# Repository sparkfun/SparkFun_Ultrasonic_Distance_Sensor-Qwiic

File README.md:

SparkFun Ultrasonic Distance Sensor - TCT40 (Qwiic) 
========================================

<center></center>

[*SparkFun Ultrasonic Distance Sensor - TCT40 (Qwiic) (SEN-24805)*](https://www.sparkfun.com/products/24805)

The SparkFun Qwiic Ultrasonic Distance Sensor, a user-friendly upgrade to the popular HC-SR04 sensor, offers non-contact distance measurement from 2cm to 400cm with an accuracy of 3mm. This sensor is designed to seamlessly integrate with the Qwiic ecosystem for I<sup>2</sup>C communication, making it a breeze to add to your existing projects and daisy-chain with other Qwiic components.

If you prefer to bypass the Qwiic connector and I2C, you can also access the VCC, Trigger, Echo, and Ground pins broken out on the board's edge. Please be aware that this ultrasonic sensor comes uncalibrated, and you will need to manipulate the raw output for your specific application.

With its wide range of applications, the SparkFun Qwiic Ultrasonic Distance Sensor is a versatile tool for robotics projects, obstacle avoidance systems, and any application that requires accurate distance measurement without physical contact. Its adaptability makes it a valuable addition to your toolkit.

Repository Contents
-------------------

* **/Documentation** - Datasheets, additional product information
* **/Enclosure** - Enclosure files 
* **/Firmware** - Default firmware on the Ultrasonic Distance Sensor -TCT40 
* **/Hardware** - Eagle design files (.brd, .sch)
* **/Production** - Production panel files (.brd)

Documentation
--------------
* **[Hookup Guide](https://docs.sparkfun.com/SparkFun_Ultrasonic_Distance_Sensor-Qwiic)** - Basic hookup guide for the SparkFun Ultrasonic Distance Sensor - TCT40 (Qwiic).
* **[Arduino Library](https://github.com/sparkfun/SparkFun_Qwiic_Ultrasonic_Arduino_Library)** - Arduino library for the SparkFun Ultrasonic Distance Sensor - TCT40 (Qwiic). 

License Information
-------------------

This product is _**open source**_! 

Please review the LICENSE.md file for license information. 

If you have any questions or concerns on licensing, please contact technical support on our [SparkFun forums](https://forum.sparkfun.com/viewforum.php?f=152).

Distributed as-is; no warranty is given.

- Your friends at SparkFun.

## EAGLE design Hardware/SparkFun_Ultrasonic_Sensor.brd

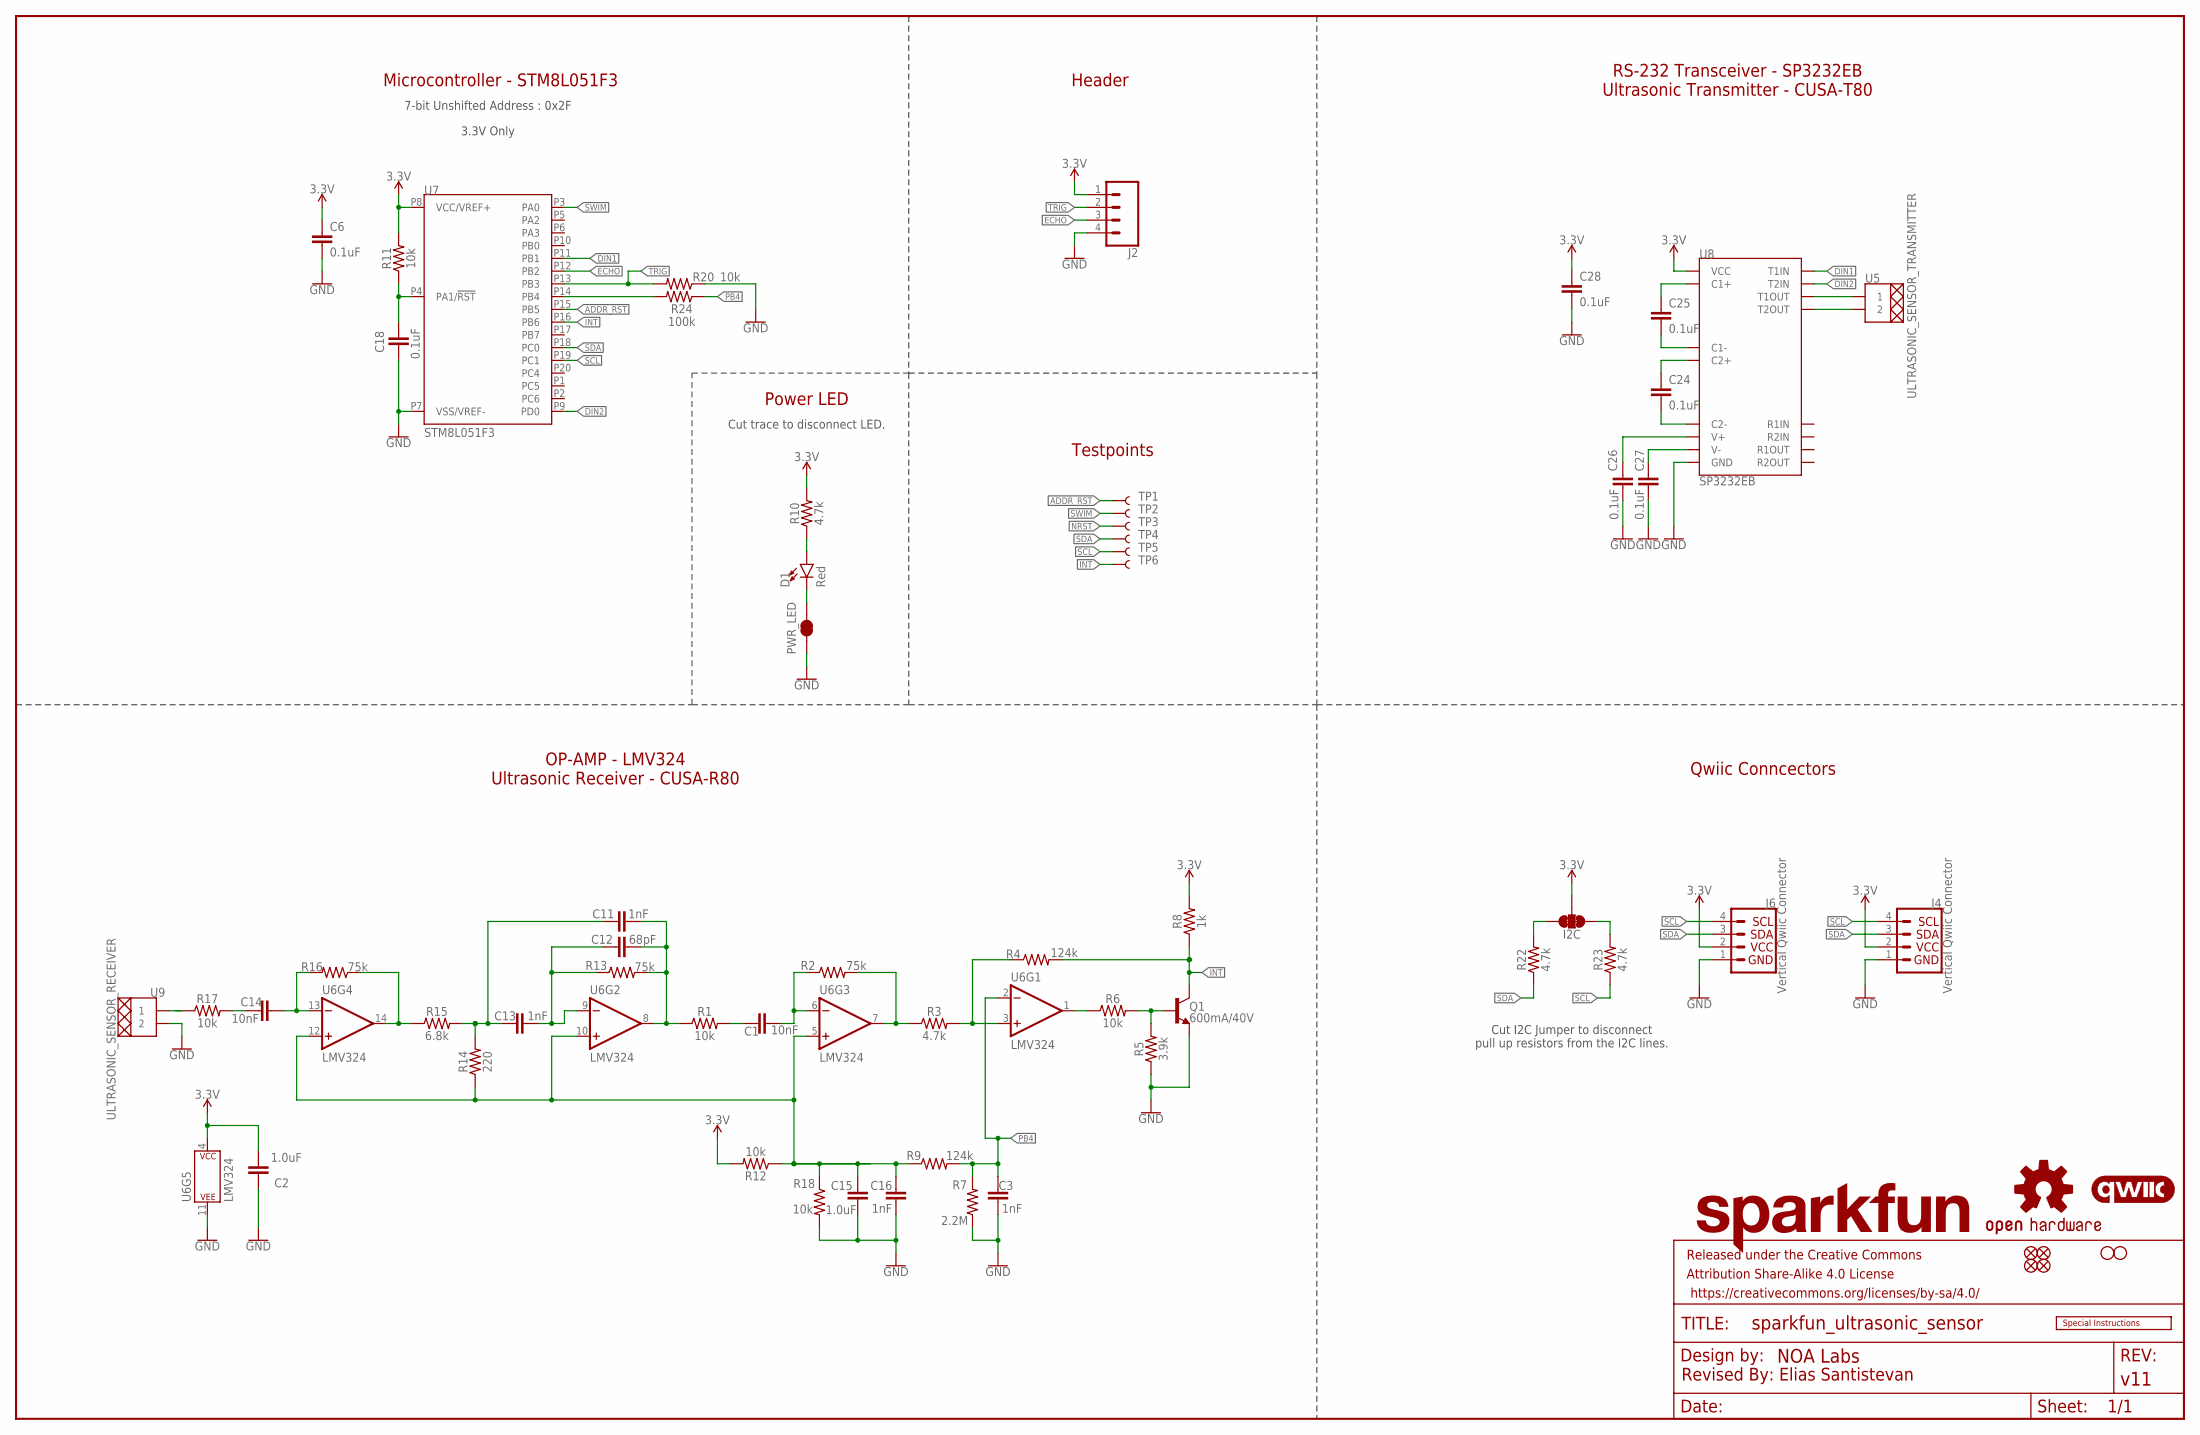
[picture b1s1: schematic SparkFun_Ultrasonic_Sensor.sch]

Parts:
C1, C14: 10nF; 0603
C2, C15: 1.0uF; 0603
C3, C11, C13, C16: 1nF; 0603
C6, C18, C24, C25, C26, C27, C28: 0.1uF; 0603
C12: 68pF; 0603
D1: Red; LED-0603
FD1, FD2, FD3, FD4: FIDUCIAL1X2; FIDUCIAL-1X2
FRAME1: FRAME-LEDGER; CREATIVE_COMMONS
H1, H2: STAND-OFFTIGHT; STAND-OFF-TIGHT
I2C: JUMPER-SMT_3_2-NC_TRACE_SILK; SMT-JUMPER_3_2-NC_TRACE_SILK
J2: CONN_041X04_NO_SILK_NO_POP; 1X04_NO_SILK
J4, J6: Vertical Qwiic Connector; JST04_1MM_VERT
LOGO1: SPECIAL_INSTRUCTIONS-ORDERING; ORDERING_INSTRUCTIONS
LOGO2: SFE_LOGO_NAME.1_INCH; SFE_LOGO_NAME_.1
LOGO3: QWIIC_LOGO_3MM; QWIIC_3MM
LOGO4: OSHW-LOGOS; OSHW-LOGO-S
PWR_LED: JUMPER-SMT_2_NC_TRACE_SILK; SMT-JUMPER_2_NC_TRACE_SILK
Q1: 600mA/40V; SOT23-3
R1, R6, R11, R12, R17, R18, R20: 10k; 0603
R2, R13, R16: 75k; 0603
R3, R10, R22, R23: 4.7k; 0603
R4, R9: 124k; 0603
R5: 3.9k; 0603
R7: 2.2M; 0603
R8: 1k; 0603
R14: 220; 0603
R15: 6.8k; 0603
R24: 100k; 0603
TP1, TP2, TP3, TP4, TP5, TP6: TEST-POINT3X5; PAD.03X.05
U5: ULTRASONIC_SENSOR_TRANSMITTER; CUSA-T80
U6: LMV324; SO14
U7: STM8L051F3; TSSOP20
U8: SP3232EB; TSSOP16
U9: ULTRASONIC_SENSOR_RECEIVER; CUSA-R80

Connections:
3.3V: C2.2, C6.1, C28.1, I2C.2, J2.1, J4.2, J6.2, R8.2, R10.2, R11.2, R12.2, U6.4 (P$V+), U7.P8 (VCC/VREF+), U8.P16 (VCC)
ADDR_RST: TP1.1, U7.P15 (PB5)
DIN1: U7.P11 (PB1), U8.P11 (T1IN)
DIN2: U7.P9 (PD0), U8.P10 (T2IN)
ECHO: J2.3, U7.P12 (PB2)
GND: C2.1, C3.2, C6.2, C15.1, C16.1, C18.2, C26.2, C27.2, C28.2, J2.4, J4.1, J6.1, PWR_LED.1, Q1.2 (E), R5.1, R7.1, R18.2, R20.1, U6.11 (P$V-), U7.P7 (VSS/VREF-), U8.P15 (GND), U9.P2 (2)
INT: Q1.3 (C), R4.2, R8.1, TP6.1, U7.P16 (PB6)
N: R24.2, U7.P14 (PB4)
unnamed: R2.2, R3.1, U6.7 (OUT)
unnamed: C1.1, R2.1, U6.6 (-IN)
unnamed: C1.2, R1.2
unnamed: R3.2, R4.1, U6.3 (+IN)
unnamed: Q1.1 (B), R5.2, R6.2
unnamed: R6.1, U6.1 (OUT)
unnamed: D1.A, R10.1
unnamed: C25.1, U8.P1 (C1+)
unnamed: C12.1, C13.1, R13.1, U6.9 (-IN)
unnamed: C11.2, C12.2, R1.1, R13.2, U6.8 (OUT)
unnamed: D1.C, PWR_LED.2
unnamed: C11.1, C13.2, R14.2, R15.2
unnamed: R15.1, R16.1, U6.14 (OUT)
unnamed: C14.1, R16.2, U6.13 (-IN)
unnamed: C14.2, R17.2
unnamed: I2C.3, R22.2
unnamed: I2C.1, R23.2
unnamed: R17.1, U9.P1 (1)
unnamed: C15.2, C16.2, R9.1, R12.1, R14.1, R18.1, U6.5 (+IN), U6.10 (+IN), U6.12 (+IN)
unnamed: C25.2, U8.P3 (C1-)
unnamed: C24.1, U8.P4 (C2+)
unnamed: C24.2, U8.P5 (C2-)
unnamed: C27.1, U8.P6 (V-)
unnamed: C26.1, U8.P2 (V+)
unnamed: U5.P1 (1), U8.P14 (T1OUT)
unnamed: U5.P2 (2), U8.P7 (T2OUT)
NRST: C18.1, R11.1, TP3.1, U7.P4 (PA1/!RST!)
PB4: C3.1, R7.2, R9.2, R24.1, U6.2 (-IN)
SCL: J4.4, J6.4, R23.1, TP5.1, U7.P19 (PC1)
SDA: J4.3, J6.3, R22.1, TP4.1, U7.P18 (PC0)
SWIM: TP2.1, U7.P3 (PA0)
TRIG: J2.2, R20.2, U7.P13 (PB3)

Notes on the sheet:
Revised By: Elias Santistevan
Microcontroller - STM8L051F3
Testpoints
RS-232 Transceiver - SP3232EB Ultrasonic Transmitter - CUSA-T80
OP-AMP - LMV324 Ultrasonic Receiver - CUSA-R80
Qwiic Conncectors
Header
Cut I2C Jumper to disconnect pull up resistors from the I2C lines.
7-bit Unshifted Address : 0x2F
3.3V Only
Power LED
Cut trace to disconnect LED.

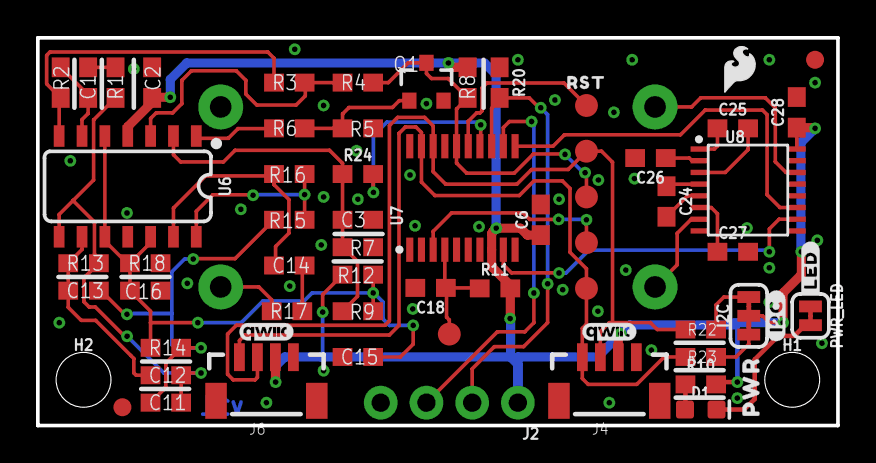
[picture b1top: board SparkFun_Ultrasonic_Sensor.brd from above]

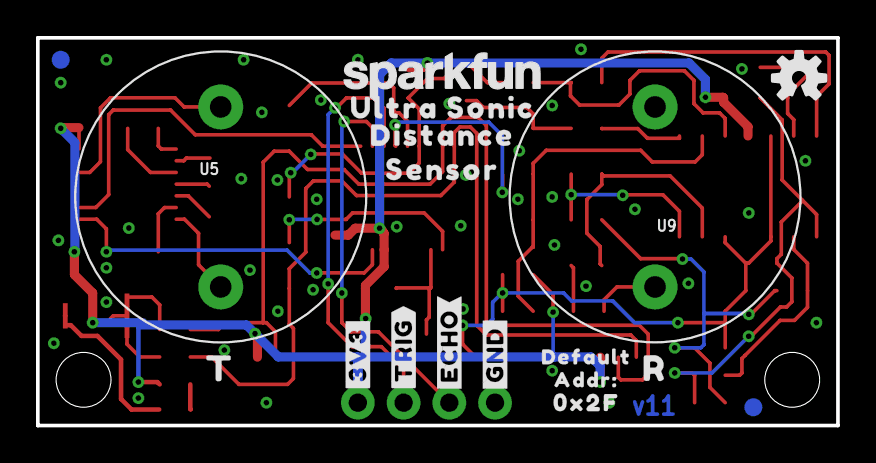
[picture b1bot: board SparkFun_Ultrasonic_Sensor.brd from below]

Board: 2 copper layers, 44.5 x 21.5 mm, 85 parts (18 on the bottom side), 40 nets.

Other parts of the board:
U$1: #ECHO#0
U$2: #TRIG#1
U$3: #GND#4
U$4: #3V3#2
U$5: QWIIC_3MM
U$6: SFE_LOGO_FLAME_.1
U$7: #I2C#16
U$8: T103
U$9: R104
U$10: DISTANCE101
U$11: ULTRA_SONIC100
U$12: SENSOR102
U$13: DEFAULT129
U$14: ADDR#130
U$15: 0X2F131
U$16: PWR17
U$17: #LED#15
U$18: RST132

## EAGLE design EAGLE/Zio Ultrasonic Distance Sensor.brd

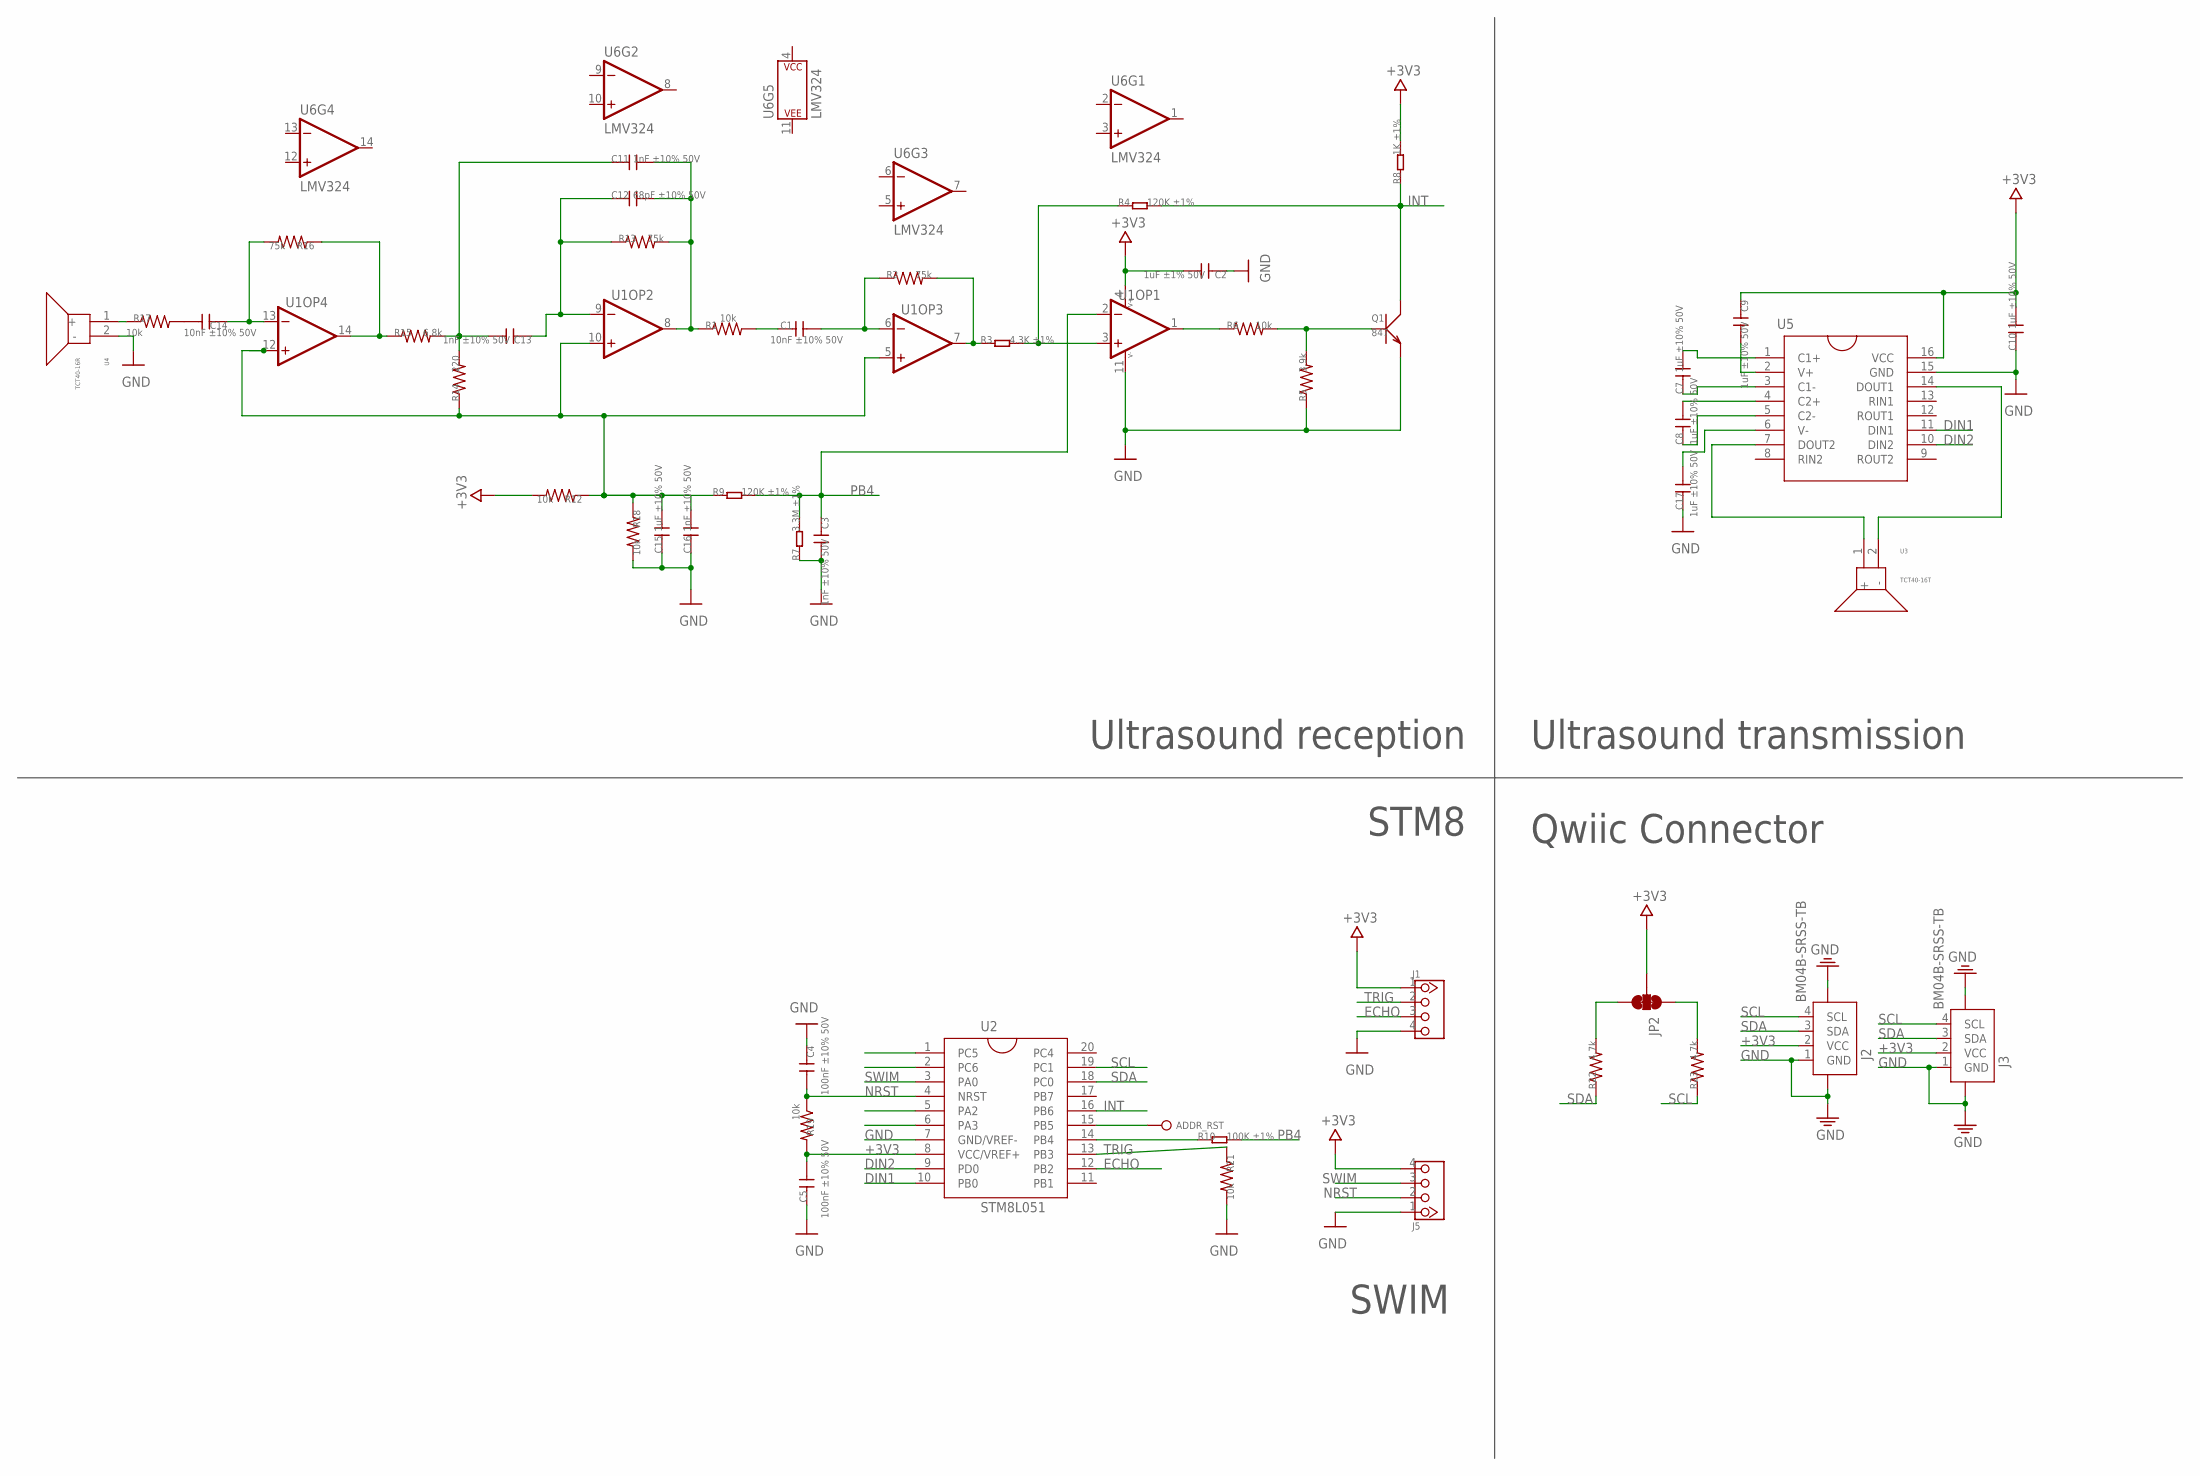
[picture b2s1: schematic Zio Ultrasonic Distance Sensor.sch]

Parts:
ADDR_RST: TEST_POINT35MIL; 1P-35MIL
C1, C14: 10nF ±10% 50V; 0603
C2: 1uF ±1% 50V; 0603
C3, C11, C13, C16: 1nF ±10% 50V; 0603
C4, C5: 100nF ±10% 50V; 0603
C7, C8, C9, C10, C15, C17: 1uF ±10% 50V; 0603
C12: 68pF ±10% 50V; 0603
J1: HEADER-4P-60/35MIL; 4P-65/35MIL
J2, J3: BM04B-SRSS-TB; JST-SH-4P-90
J5: HEADER-4P-TEST_3.08_4P; TEST_3.08_4P
JP2: SMT-JUMPER_3_2-NC_TRACE
Q1: 847; SOT23
R1, R6, R12, R17, R18, R19, R21: 10k; 0603
R2, R13, R16: 75k; 0603
R3: 4.3K ±1%; 0603
R4, R9: 120K ±1%; 0603
R5: 3.9k; 0603
R7: 3.3M ±1%; 0603
R8: 1K ±1%; 0603
R10: 100K ±1%; 0603
R14: 220; 0603
R15: 6.8k; 0603
R22, R23: 4.7k; 0603
U1: LMV324; SO014
U2: STM8L051; TSSOP20
U3: TCT40-16T; TCT40-16T/R
U4: TCT40-16R; TCT40-16T/R
U5: UT3232G-S16-RSOIC-16; SOIC16
U6: LMV324; SO14

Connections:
+3V3: C2.2, C5.1, C9.1, C10.2, J1.1, J2.2 (VCC), J3.2 (VCC), J5.4, JP2.2, R8.2, R12.2, R19.2, U1.4 (V+), U2.8 (VCC/VREF+), U5.16 (VCC)
DIN1: U2.10 (PB0), U5.11 (DIN1)
DIN2: U2.9 (PD0), U5.10 (DIN2)
ECHO: J1.3, U2.12 (PB2)
GND: C2.1, C3.2, C4.1, C5.2, C10.1, C15.1, C16.1, C17.1, J1.4, J2.1 (GND), J2.5, J2.6, J3.1 (GND), J3.5, J3.6, J5.1, Q1.2 (E), R5.1, R7.1, R18.2, R21.2, U1.11 (V-), U2.7 (GND/VREF-), U4.2 (-), U5.15 (GND)
INT: Q1.3 (C), R4.2, R8.1, U2.16 (PB6)
unnamed: R2.2, R3.1, U1.7 (OUT)
unnamed: C1.1, R2.1, U1.6 (IN-)
unnamed: C1.2, R1.2
unnamed: R3.2, R4.1, U1.3 (IN+)
unnamed: Q1.1 (B), R5.2, R6.2
unnamed: R6.1, U1.1 (OUT)
unnamed: C7.2, U5.1 (C1+)
unnamed: C12.1, C13.1, R13.1, U1.9 (IN-)
unnamed: C11.2, C12.2, R1.1, R13.2, U1.8 (OUT)
unnamed: C15.2, C16.2, R9.1, R12.1, R14.1, R18.1, U1.5 (IN+), U1.10 (IN+), U1.12 (IN+)
unnamed: C11.1, C13.2, R14.2, R15.2
unnamed: C7.1, U5.3 (C1-)
unnamed: R15.1, R16.1, U1.14 (OUT)
unnamed: C14.1, R16.2, U1.13 (IN-)
unnamed: C14.2, R17.2
unnamed: C8.2, U5.4 (C2+)
unnamed: C8.1, U5.5 (C2-)
unnamed: JP2.3, R22.2
unnamed: JP2.1, R23.2
unnamed: C9.2, U5.2 (V+)
unnamed: C17.2, U5.6 (V-)
unnamed: U3.2 (-), U5.14 (DOUT1)
unnamed: U3.1 (+), U5.7 (DOUT2)
unnamed: R17.1, U4.1 (+)
unnamed: ADDR_RST.P$1, U2.15 (PB5)
unnamed: R10.1, U2.14 (PB4)
NRST: C4.2, J5.2, R19.1, U2.4 (NRST)
PB4: C3.1, R7.2, R9.2, R10.2, U1.2 (IN-)
SCL: J2.4 (SCL), J3.4 (SCL), R23.1, U2.19 (PC1)
SDA: J2.3 (SDA), J3.3 (SDA), R22.1, U2.18 (PC0)
SWIM: J5.3, U2.3 (PA0)
TRIG: J1.2, R21.1, U2.13 (PB3)

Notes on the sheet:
SWIM
Qwiic Connector
Ultrasound transmission
Ultrasound reception
STM8

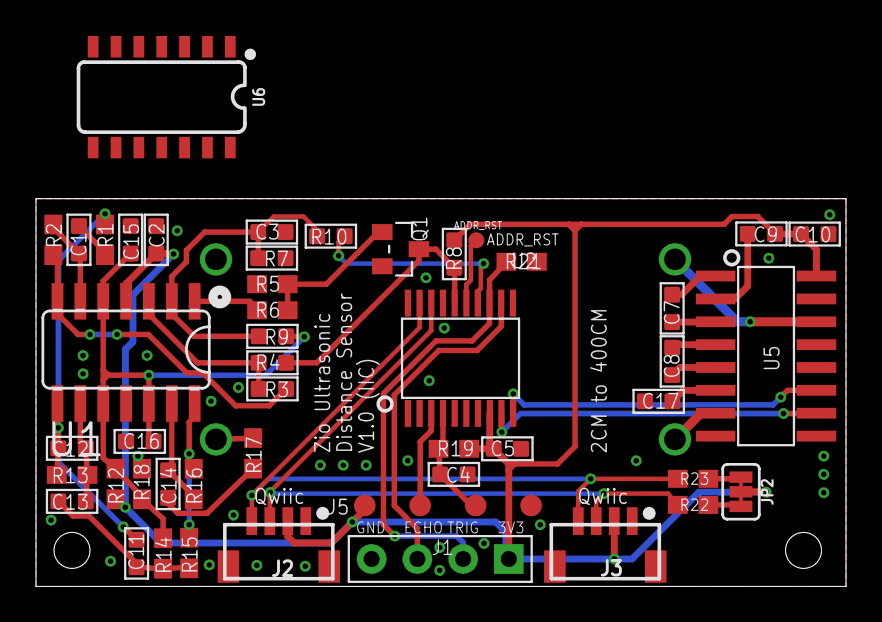
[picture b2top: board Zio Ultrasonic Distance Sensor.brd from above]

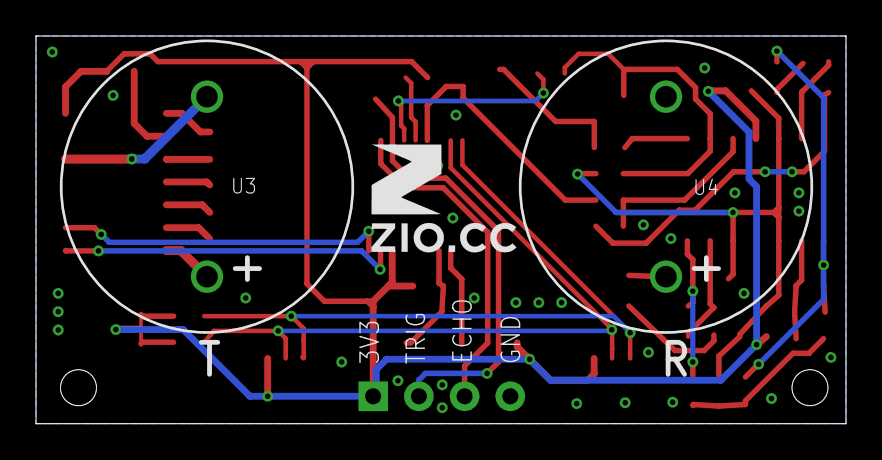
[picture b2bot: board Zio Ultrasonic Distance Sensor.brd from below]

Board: 2 copper layers, 45.0 x 21.5 mm, 51 parts (3 on the bottom side), 38 nets.

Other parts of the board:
U$5: 6MM

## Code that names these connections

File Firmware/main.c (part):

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}

/*
 * @brief GPIO setup for the ultrasonic sensor: DIN1, DIN2, ECHO, PB4 and interrupts pins TRIG, INT, and ADDR_RST.
 * @param  None
 * @retval None
 */
void initializeGPIO(void)
{
    GPIO_Init(GPIOD, (GPIO_Pin_TypeDef)GPIO_Pin_0, GPIO_Mode_Out_PP_High_Fast); // DIN2
    GPIO_Init(GPIOB, (GPIO_Pin_TypeDef)GPIO_Pin_1, GPIO_Mode_Out_PP_High_Fast); // DIN1
    GPIO_Init(GPIOB, (GPIO_Pin_TypeDef)GPIO_Pin_2, GPIO_Mode_Out_PP_Low_Fast);  // ECHO
    GPIO_Init(GPIOB, (GPIO_Pin_TypeDef)GPIO_Pin_4, GPIO_Mode_Out_PP_Low_Slow);  // PB4
    GPIO_Init(GPIOB, (GPIO_Pin_TypeDef)GPIO_Pin_3, GPIO_Mode_In_FL_IT);         // TRIG
    GPIO_Init(GPIOB, (GPIO_Pin_TypeDef)GPIO_Pin_5, GPIO_Mode_In_PU_IT);         // ADDR_RST
    GPIO_Init(GPIOB, (GPIO_Pin_TypeDef)GPIO_Pin_6, GPIO_Mode_In_FL_IT);         // INT

    // External interrups for TRIG, INT, ADDR_RST
    EXTI_DeInit();
    EXTI_SetPinSensitivity(EXTI_Pin_3, EXTI_Trigger_Rising);  // TRIG
    EXTI_SetPinSensitivity(EXTI_Pin_5, EXTI_Trigger_Falling); // ADDR_RST
    EXTI_SetPinSensitivity(EXTI_Pin_6, EXTI_Trigger_Rising);  // INT
}

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
        delay(kCycles48kHz);
    }
    // ECHO pin high
    GPIO_ResetBits(GPIOB, GPIO_Pin_2);
    TIM2_SetCounter(0);
    TIM4_SetCounter(0);
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{
    if (enable)
    {
        GPIO_Init(GPIOB, (GPIO_Pin_TypeDef)GPIO_Pin_4, GPIO_Mode_Out_PP_Low_Fast); // PB4
        GPIO_ResetBits(GPIOB, GPIO_Pin_4);
    }
    else
    {
        GPIO_Init(GPIOB, (GPIO_Pin_TypeDef)GPIO_Pin_4, GPIO_Mode_Out_PP_Low_Fast); // PB4
        GPIO_SetBits(GPIOB, GPIO_Pin_4);
    }
}
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
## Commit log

2023-12-07 Original design commit
2024-01-10 Removes old gerbers, adds some new parts
2024-01-10 Adds new ultrasonic receiver and transmitter and new RS232 IC
2024-01-11 Renames folders
2024-01-11 Removes older files - previous commit also added Documents
2024-01-11 Renames hardware files
2024-01-11 Adds tkeepout to ultrasonic sensors
2024-01-12 Removes almost any lingering parts from old design. Gets close to finishing schematic
2024-01-12 Finishes up schematic
2024-01-12 Moves passives around the PCB
2024-01-12 Moves design to origin, routes most signals
2024-01-12 Routes more wires
2024-01-15 Finishes routing the board.
2024-01-15 Adds more vias
2024-01-15 Adds silk
2024-01-15 Adds ordering instructions
2024-01-15 Adds measures
2024-01-15 Changes the size and placement of parts so that they sit at reasonable dimensions
2024-01-15 Moves SparkFun logo
2024-01-15 Adds a few more measures
2024-01-15 Adds version number
2024-01-15 Moves the odering instructions away from the design
2024-01-16 Fixes various schematic elements, some acid traps, and improves ground pour
2024-01-16 Moves a number of parts to away from the Ultrasonic sensor plated holes
2024-01-16 Moves some more parts away from the sensor through holes and updates the schematic
2024-01-22 Adds power LED, RXT silk, and increases the size of the tespoints.
2024-01-22 Adds SKUs to new parts
2024-01-22 Adds parts with new SKUs to design
2024-01-22 Adds some silk
2024-01-22 Adds Production Files
2024-01-22 Changes production file zip file to include version
2024-01-30 Adds some notes on the op-amp stages
2024-01-30 Adds some better spacing
2024-02-14 Moves some files around
2024-03-04 Puts the interrups files in the correct directory
2024-03-04 Updates all of the C files from ST
2024-03-04 Updates the remaining C fiels
2024-03-04 Updates config file
2024-03-04 Adds interrupt vector file - many of the handlers will need to be removed
2024-03-04 Updates interrupts and pins
2024-03-04 Updates GPIO, defines part number for compiler
2024-03-05 Files are linking, but there is simply too many items .text size overflow error
2024-03-05 Comments out various libraries that I'm not using
2024-03-05 Comments out more includes
2024-03-05 Still too large
2024-03-07 Reduces the size of many libraries so that it fits onto the MCU
2024-03-07 Removes the I2C function and replaces it with API calls
2024-03-09 Rewrites I2C interrupt function
2024-04-08 various changes, many missed commits later
2024-04-08 Removes object files from repository - will now be ignored
2024-04-29 Updates the board files with the new part names
2024-04-30 Debugging update
2024-04-30 Removes bsp files, moves functions to main, adds main.h
    * Reduces the size of the code within the interrupts
    * Adds interrupt flags for the numerous interrupts
    * Moves all actions to the main loop
2024-04-30 Adds function for enabling and setting timers
2024-04-30 Updates prototype names for functions defined in main
2024-04-30 Updates the interrupt variable names to better understand what they are
2024-04-30 Replaces command variables with better naming convention
2024-04-30 Adds forgotten return type for setTimers
2024-04-30 Adds preprocessor guards
2024-05-01 Fixes multiple defintions of symbol error
    * variables were being shared between two files and logically I thought to include the same header file across to .c files. This however, was causing the variable to be compiled by TWO translation un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
2024-05-01 fixes the various naming conventions of constants and functions
2024-05-01 Updates more variable names
2024-05-01 Fixes unchanged variables to the upated ones
2024-05-02 Removes extraneous files
2024-05-02 Adds reference manual
2024-05-05 Uses switch/case in i2c interrupt, increases i2c speed to 100kHz
2024-05-06 Uncomments the "enableINterrupts"
2024-05-10 Initial Pass of Documentation for V11
2024-05-10 Updates for build
2024-05-15 Fixes the interrupt vector table
2024-05-20 Fixes enable variable
2024-05-21 Ensures all timers work
2024-05-22 Fixes delay in pulsetransmitter
2024-05-22 changes some variable names, updates functions for changing the i2c address.
2024-05-23 Removes another magic number, fixes some floating point integer operations
2024-05-23 Fixes the #define bug where I forgot parentheses which led to unknown behavior
2024-05-24 Updates code to reflect the pin used on new design
2024-05-24 Renames examples, fixes to trigger based readings
2024-05-25 Finalizes writing address to EEPROM, adds change address example
2024-05-25 Fixes small bug
2024-05-25 Removes old hex file, updates design with correct pin names on RS-232 transceiver
2024-05-26 Fixes trigger interrupt
2024-05-27 Adds comments
2024-05-28 Fixes small typo
2024-05-28 Removes arduino examples - moved to arduino library repository
2024-05-28 Formats code
2024-05-28 Removes second for loop for one single for loop
2024-05-30 Changes some if statements to else if
    * Renames some constants
    * Adds better notes on the delay function
    * Localizes some variables to their code blocks
2024-05-30 Corrects indentation
2024-05-31 Adds volatile to variables that need it, adds more comments
    * Updates the name of some variable to indicate they're flags
    * Moves interrupt variables to the top of the code block they trigger
    * Swaps the ECHO pin polarity for consistency with the older product
2024-05-31 Removes .sal files
2024-05-31 Deletes another unnecessary file
2024-05-31 Fix to cycles declaration and fix to echo pin orientation
2024-05-31 Moves firmware to base firmware folder and adds v10 to name
2024-06-13 Example updates
2024-06-13 Updating example
2024-06-13 Adding Hardware Assembly photo
2024-06-13 Updating schematic and files and intro
2024-06-13 Fixing typos
2024-06-19 Adding Example 2 gif
2024-06-20 Updating links and finalizing docs
2024-06-20 Fixing links
2024-06-20 Adding Arduino Library link
2024-06-20 Fixing single page links
2024-06-20 Updating sensor range
2024-06-21 Deployed a9f4e70 with MkDocs version: 1.6.0
2024-06-21 Fixes link to Arduino library
2024-07-12 Redirect deleted branch to "main" in Arduino Library so GitHub Pages can deploy properly
2024-07-12 Update Formatting so Grid Card is Uniform in Width
2024-08-07 Deployed 4713b53 with MkDocs version: 1.6.0
2026-06-03 Deployed 05adcfd with MkDocs version: 1.6.1

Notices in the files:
Firmware/main.c:
SPDX-License-Identifier: MIT
Copyright (c) 2024 SparkFun Electronics
parts and their libraries:
SparkFun-Resistors: Licensing: Creative Commons ShareAlike 4.0 International - https://creativecommons.org/licenses/by-sa/4.0
SparkFun-Aesthetics: Released under the Creative Commons Attribution Share-Alike 4.0 License
SparkFun-Aesthetics: https://creativecommons.org/licenses/by-sa/4.0
